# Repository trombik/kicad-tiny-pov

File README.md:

# tiny-pov

A Persistence of Vision, or PoV, device using `ATTiny` and a GPIO expander,
`MCP23017`
([datasheet](https://ww1.microchip.com/downloads/en/devicedoc/20001952c.pdf)).

The project is intended for students who have mastered Arduino basics. The
code is small, and includes some advanced topics, such as `PROGMEM`, using
external libraries, `platformio` build system, and `I2C`.

## Schematic

## Requirements

* python 3.x
* [tox](https://tox.wiki/en/latest/)
* An [Arduino as ISP](https://docs.arduino.cc/built-in-examples/arduino-isp/ArduinoISP) programmer

## Usage

Install `platformio`, the toolchain and packages for AVR MCUs. `tox` does
everything and build the project.

```console
tox
```

To run `platformio`, you need to activate the python virtual environment:

```console
source .tox/python/bin/activate
```

Build the project:

```console
pio run
```

Upload the code:

```console
pio run -t upload --upload-port ${SERIAL_PORT}
```

Replace `${SERIAL_PORT}` with the serial port on local machine.
`/dev/ttyUSB${N}` for Linux, `/dev/cuaU${N}` for FreeBSD, `COM${N}` for
Windows.

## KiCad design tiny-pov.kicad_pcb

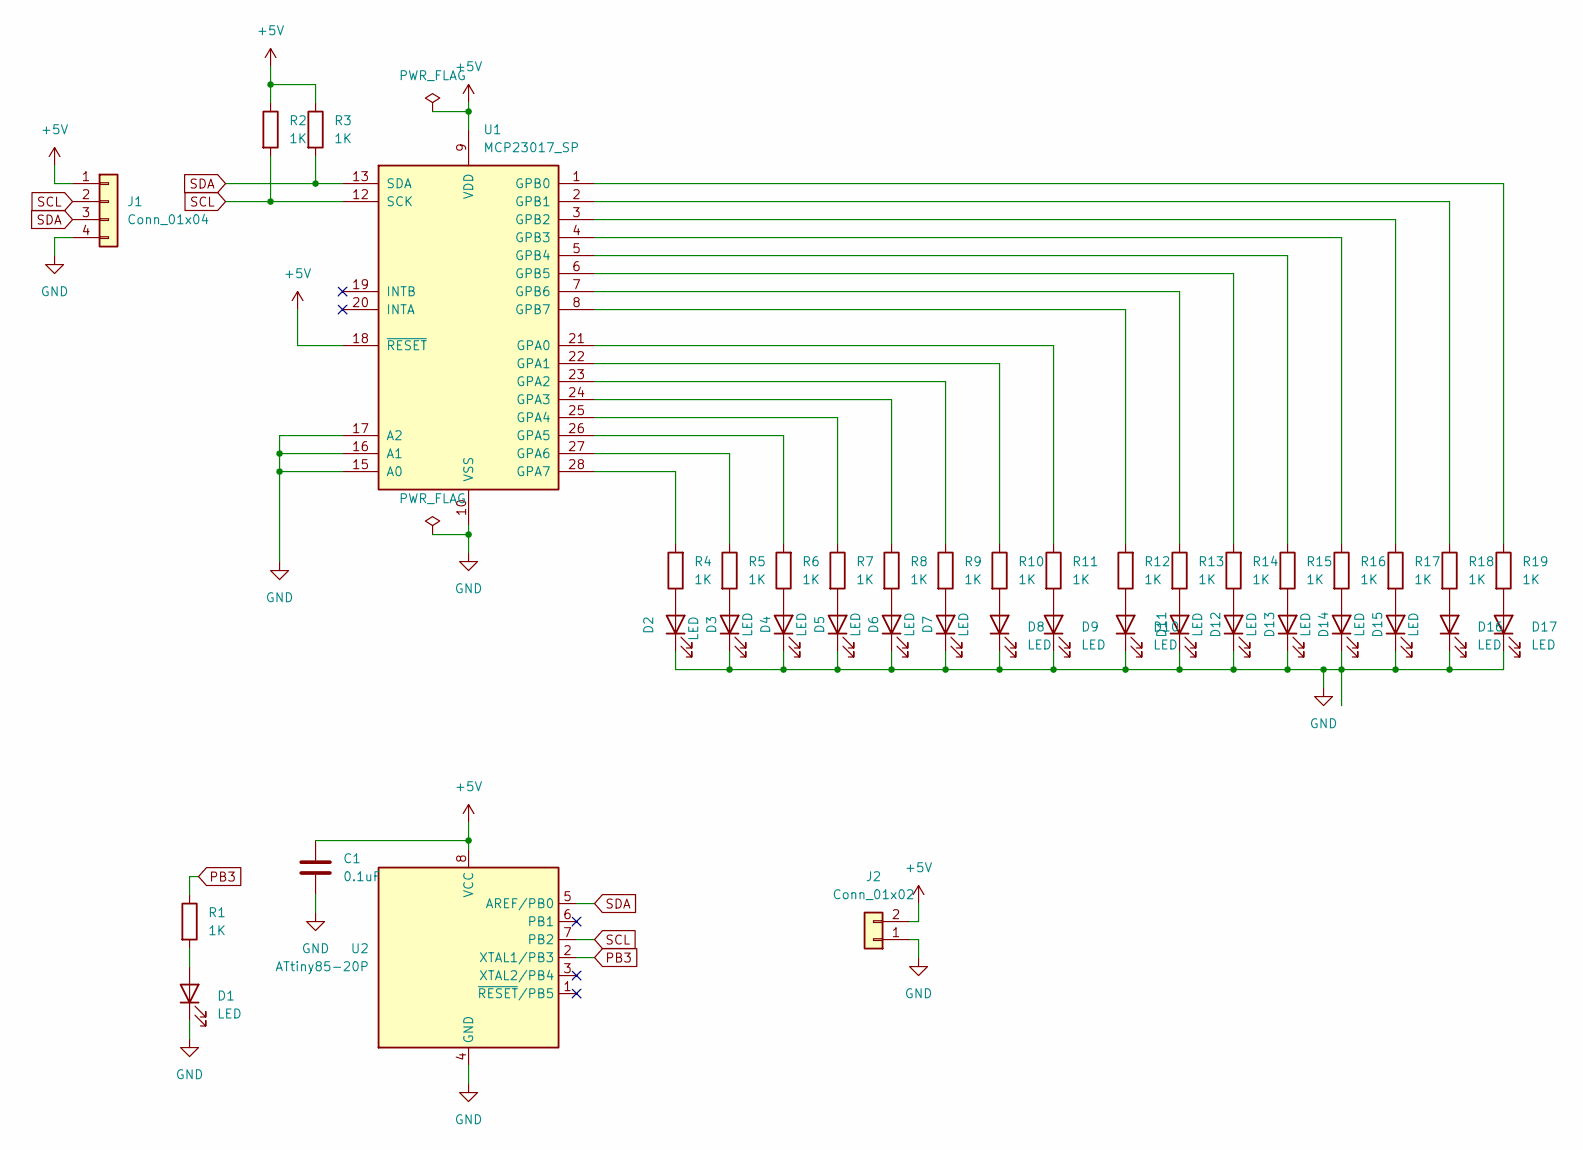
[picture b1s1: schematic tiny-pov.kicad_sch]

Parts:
C1: 0.1uF; C_Disc_D6.0mm_W2.5mm_P5.00mm
D1, D2, D3, D4, D5, D6, D7, D8, D9, D10, D11, D12, D13, D14, D15, D16, D17: LED; LED_D3.0mm
J1: Conn_01x04; JST_XH_B4B-XH-A_1x04_P2.50mm_Vertical
J2: Conn_01x02; JST_XH_B2B-XH-A_1x02_P2.50mm_Vertical
R1, R2, R3, R4, R5, R6, R7, R8, R9, R10, R11, R12, R13, R14, R15, R16, R17, R18, R19: 1K; R_Axial_DIN0207_L6.3mm_D2.5mm_P7.62mm_Horizontal
U1: MCP23017_SP; DIP-28_W7.62mm
U2: ATtiny85-20P; DIP-8_W7.62mm

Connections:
+5V: C1.1, J1.1, J2.2, R2.1, R3.1, U1.9 (VDD), U1.18 (~RESET), U2.8 (VCC)
GND: C1.2, D1.1 (K), D2.1 (K), D3.1 (K), D4.1 (K), D5.1 (K), D6.1 (K), D7.1 (K), D8.1 (K), D9.1 (K), D10.1 (K), D11.1 (K), D12.1 (K), D13.1 (K), D14.1 (K), D15.1 (K), D16.1 (K), D17.1 (K), J1.4, J2.1, U1.10 (VSS), U1.15 (A0), U1.16 (A1), U1.17 (A2), U2.4 (GND)
unnamed: D1.2 (A), R1.2
unnamed: D2.2 (A), R4.1
unnamed: D3.2 (A), R5.2
unnamed: D4.2 (A), R6.1
unnamed: D5.2 (A), R7.2
unnamed: D6.2 (A), R8.2
unnamed: D7.2 (A), R9.2
unnamed: D8.2 (A), R10.2
unnamed: D9.2 (A), R11.2
unnamed: D10.2 (A), R12.1
unnamed: D11.2 (A), R13.2
unnamed: D12.2 (A), R14.1
unnamed: D13.2 (A), R15.2
unnamed: D14.2 (A), R16.2
unnamed: D15.2 (A), R17.2
unnamed: D16.2 (A), R18.2
unnamed: D17.2 (A), R19.2
unnamed: R4.2, U1.28 (GPA7)
unnamed: R5.1, U1.27 (GPA6)
unnamed: R6.2, U1.26 (GPA5)
unnamed: R7.1, U1.25 (GPA4)
unnamed: R8.1, U1.24 (GPA3)
unnamed: R9.1, U1.23 (GPA2)
unnamed: R10.1, U1.22 (GPA1)
unnamed: R11.1, U1.21 (GPA0)
unnamed: R12.2, U1.8 (GPB7)
unnamed: R13.1, U1.7 (GPB6)
unnamed: R14.2, U1.6 (GPB5)
unnamed: R15.1, U1.5 (GPB4)
unnamed: R16.1, U1.4 (GPB3)
unnamed: R17.1, U1.3 (GPB2)
unnamed: R18.1, U1.2 (GPB1)
unnamed: R19.1, U1.1 (GPB0)
PB3: R1.1, U2.2 (XTAL1/PB3)
SCL: J1.2, R2.2, U1.12 (SCK), U2.7 (PB2)
SDA: J1.3, R3.2, U1.13 (SDA), U2.5 (AREF/PB0)

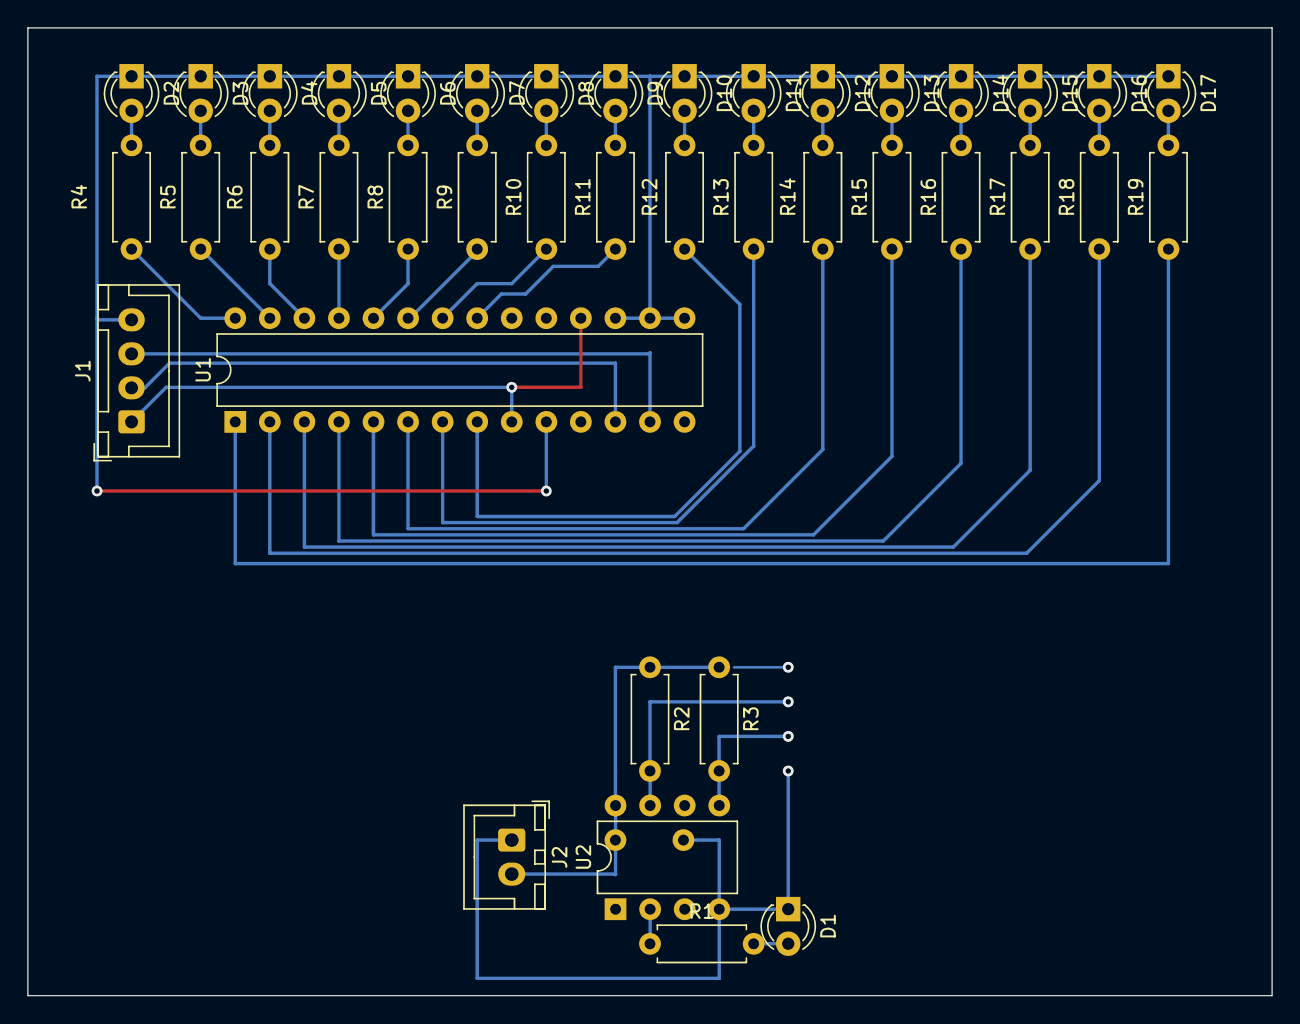
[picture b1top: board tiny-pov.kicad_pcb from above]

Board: 2 copper layers, 91.4 x 71.1 mm, 41 parts (1 on the bottom side), 38 nets.

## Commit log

2022-07-20 initial import
2022-07-20 doc: add a link to user manual for PROGMEM
2022-07-20 doc: add README
2022-07-20 doc: add usage
2022-07-20 doc: fix a link
2022-07-20 ci: add CI
2022-07-20 doc: add schematic
2022-07-20 doc: add a programmer to requirements
